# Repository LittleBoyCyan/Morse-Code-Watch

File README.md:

# Morse-Code-Watch
모스코드 워치 프로젝트

점과 선의 단순한 표현기호를 사용한 의사소통 방법인 모스코드를 보낼 수 있는 손목시계입니다.

기능
1. 아두이노와 ATEML ATtiny85 마이크로 컨트롤러 칩을 사용해서 원하는 메시지를 출력할 수 있습니다.
2. 전세계적으로 사용하는 인터네셔널 모스코드를 사용합니다.
3. 내장된 버튼을 이용해서 모스코드를 직접 발신할 수 있습니다. LED 밝기에 따라 멀리 있는 곳에서도 인지할 수 있는 통신 수단으로 사용해보세요.

가이드
1. 전원 스위치를 켜면 아두이노 코드에 미리 입력한 메시지를 반복적으로 출력합니다.
2. 모스코드 메시지가 끝날 때까지 버튼을 누르고 있으면 수동 모드로 전환됩니다.
3. 수동모드로 전환되면 버튼을 누를 때에만 LED가 켜져서 원하는 메시지를 직접 보낼 수 있습니다.
4. 배터리가 닳아서 밝기가 줄어들면 배터리를 교체하세요. 쉽게 구매할 수 있는 2032 코인 배터리를 사용합니다.

개발자
1. 아두이노 코드를 변경해서 자유롭게 해킹하세요.
2. 기본 코드에서는 영문 대문자와 숫자만 사용할 수 있습니다. 다른 언어도 직접 추가하거나 변경 가능합니다.
3. LED에는 마이크로 컨트롤러에서 3개의 출력 포트를 사용합니다. 밝기 제어를 위해 개별적으로 사용할 수 있습니다. 디폴트 세팅은 3개를 동시에 사용합니다.
4. PCB상의 ICSP 포트르 사용해서 코드를 업로드하세요. 아두이노 우노 보드가 있다면 ArduinoISP 를 사용해서 업로드 할 수 있습니다.
5. 아두이노의 입력 포트로 사용할 수 있는 것은 버튼이 있습니다.
6. 회로와 PCB 제작을 위한 파일, 아두이노 코드를 다운받을 수 있습니다.

코드 업로드
Arduino IPS 참조
https://www.arduino.cc/en/Tutorial/ArduinoISP

Arduino UNO 와 모스코드 워치의 왼쪽 상단의 ICSP 포트와의 결선 방법입니다.

아두이노 - 모스코드 워치
13 - SCK /
12 - MISO /
11 - MOSI /
10 - RESET /
5+ - VTG /
GND - GND 

1. 최신 아두이노 IDE 기준, 메뉴의 Tools > Board > Boards Manager 에서 ATtiny 검색하여 설치
2. 업로드시 ATtiny 선택
Boards : ATtiny
Processor : ATtiny85
Clock : 1Mhz
Port : 연결된 아두이노 우노 보드 선택
Programmer : Arduino as ISP

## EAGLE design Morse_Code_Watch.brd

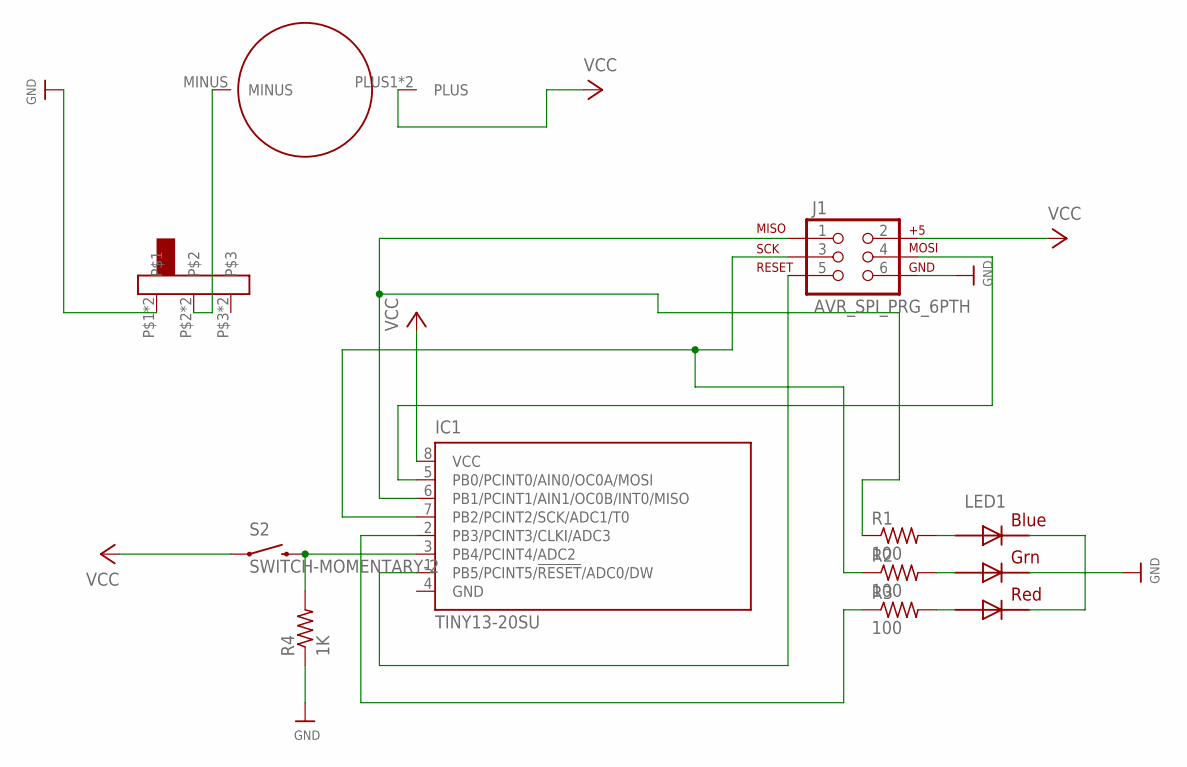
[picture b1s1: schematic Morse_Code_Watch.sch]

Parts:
IC1: TINY13-20SU; 8S2
J1: AVR_SPI_PRG_6PTH; 2X3
LED1: RGBLED5050
R1, R2, R3: 100; M2012
R4: 1K; M2012
S2: SWITCH-MOMENTARY-2; TACTILE_SWITCH_TALL
U$1: COIN_3V
U$2: SWITCH_SK-02ACTS-2235S; SWITCH_CTS-2235S

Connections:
GND: IC1.4 (GND), J1.6, LED1.4 (BLUE_C), LED1.5 (RED_C), LED1.6 (GREEN_C), R4.1, U$2.P$1, U$2.P$4
unnamed: IC1.6 (PB1/PCINT1/AIN1/OC0B/INT0/MISO), J1.1, R1.1
unnamed: IC1.5 (PB0/PCINT0/AIN0/OC0A/MOSI), J1.4
unnamed: IC1.1 (PB5/PCINT5/!RESET!/ADC0/DW), J1.5
unnamed: IC1.7 (PB2/PCINT2/SCK/ADC1/T0), J1.3, R2.1
unnamed: IC1.2 (PB3/PCINT3/CLKI/ADC3), R3.1
unnamed: IC1.3 (PB4/PCINT4/ADC2), R4.2, S2.B1 (2), S2.B2 (2)
unnamed: LED1.3 (BLUE_A), R1.2
unnamed: LED1.1 (GREEN_A), R2.2
unnamed: LED1.2 (RED_A), R3.2
unnamed: U$1.MINUS, U$2.P$2, U$2.P$5
VCC: IC1.8 (VCC), J1.2, S2.A1 (1), S2.A2 (1), U$1.PLUS1 (PLUS), U$1.PLUS2 (PLUS)

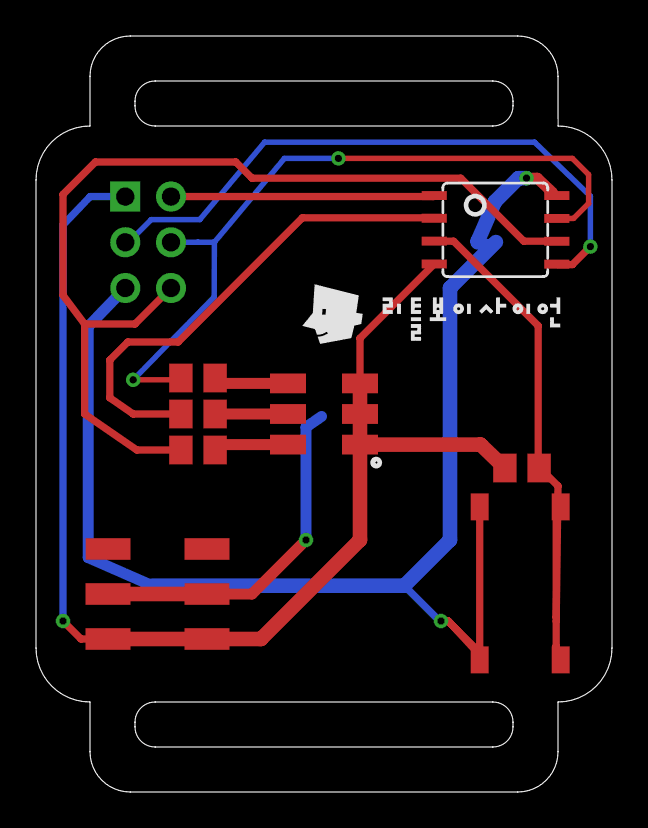
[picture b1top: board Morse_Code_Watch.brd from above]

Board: 2 copper layers, 32.0 x 42.0 mm, 11 parts (1 on the bottom side), 12 nets.

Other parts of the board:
U$8: LOGO

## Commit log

2017-12-15 Create Arduino
2017-12-18 Create eagle

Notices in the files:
parts and their libraries:
SparkFun-Connectors: Licensing: CC v3.0 Share-Alike You are welcome to use this library for commercial purposes.
